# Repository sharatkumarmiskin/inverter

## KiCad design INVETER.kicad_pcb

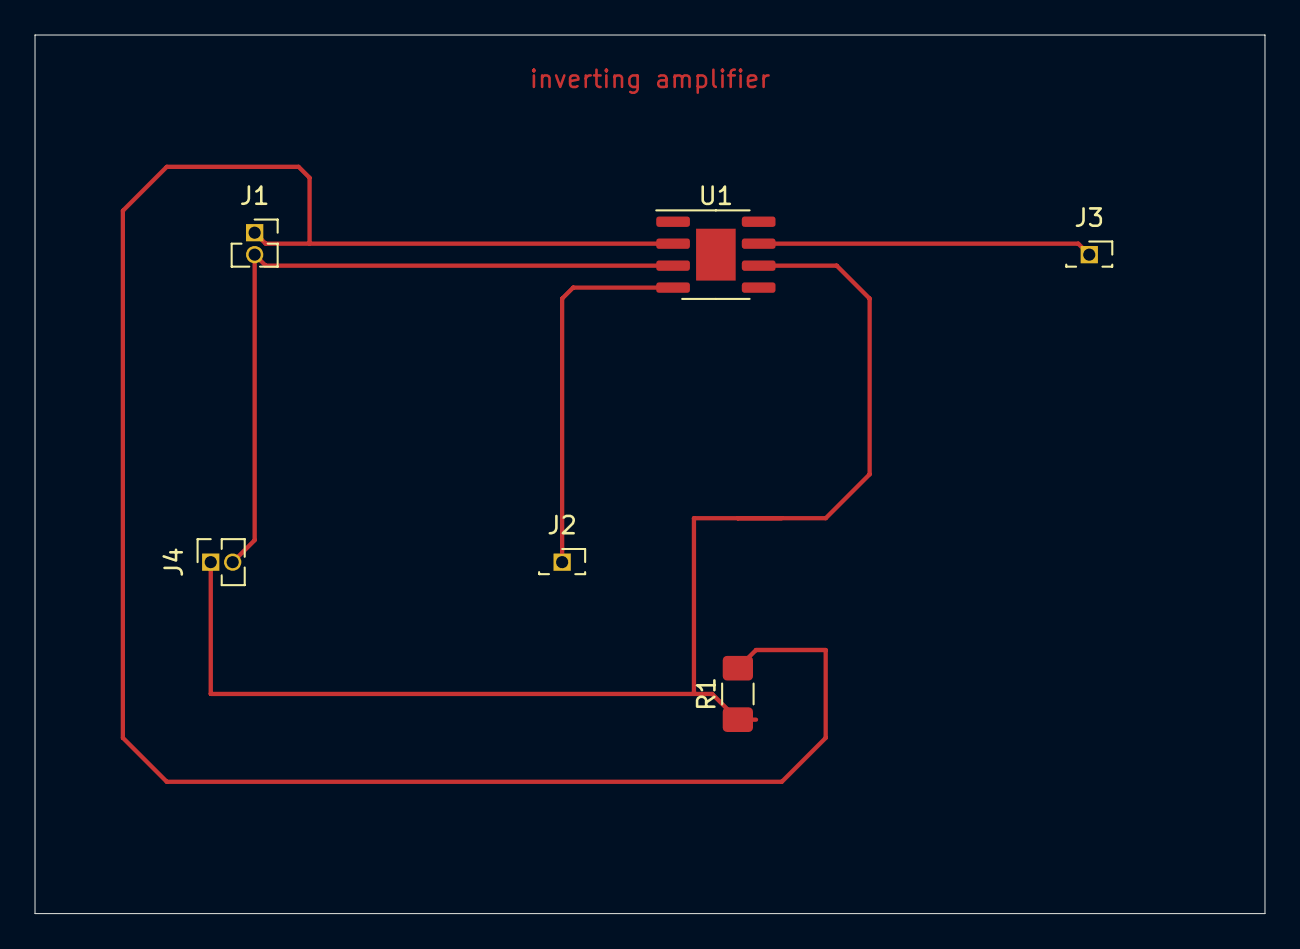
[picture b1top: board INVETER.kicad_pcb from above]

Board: 2 copper layers, 71.1 x 50.8 mm, 6 parts (0 on the bottom side), 5 nets.

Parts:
J1: Vin; PinSocket_1x02_P1.27mm_Vertical
J2: -12V; PinSocket_1x01_P1.27mm_Vertical
J3: +12V; PinSocket_1x01_P1.27mm_Vertical
J4: Vout; PinSocket_1x02_P1.27mm_Vertical
R1: R; R_1206_3216Metric_Pad1.42x1.75mm_HandSolder
U1: LM741; SOIC-8-1EP_3.9x4.9mm_P1.27mm_EP2.29x3mm

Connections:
GND: J1.2, J4.2, U1.3
unnamed: J1.1, R1.2, U1.2
unnamed: J2.1, U1.4
unnamed: J3.1, U1.7
unnamed: J4.1, R1.1, U1.6
